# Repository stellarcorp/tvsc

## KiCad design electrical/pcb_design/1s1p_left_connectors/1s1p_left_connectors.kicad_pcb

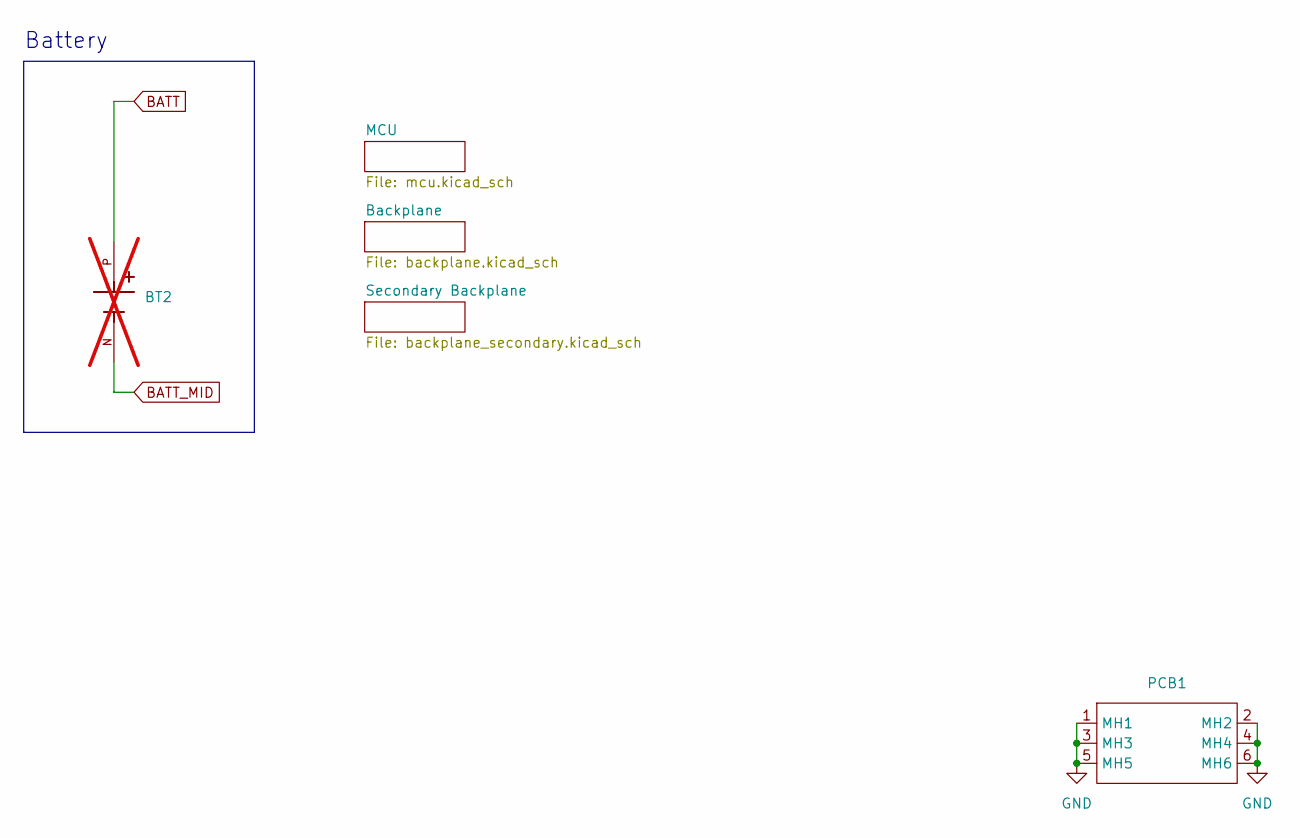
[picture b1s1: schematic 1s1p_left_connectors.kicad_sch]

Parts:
BT2: Keystone_1043; BAT_1043; Manufacturer Part Number 1043; not fitted
PCB1: Interior_Side_Panel_PCB_Shape

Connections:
BATT: BT2.P; also elsewhere on the board
BATT_MID: BT2.N; also elsewhere on the board
GND: PCB1.1 (MH1), PCB1.2 (MH2), PCB1.3 (MH3), PCB1.4 (MH4), PCB1.5 (MH5), PCB1.6 (MH6); also elsewhere on the board

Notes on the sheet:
Battery

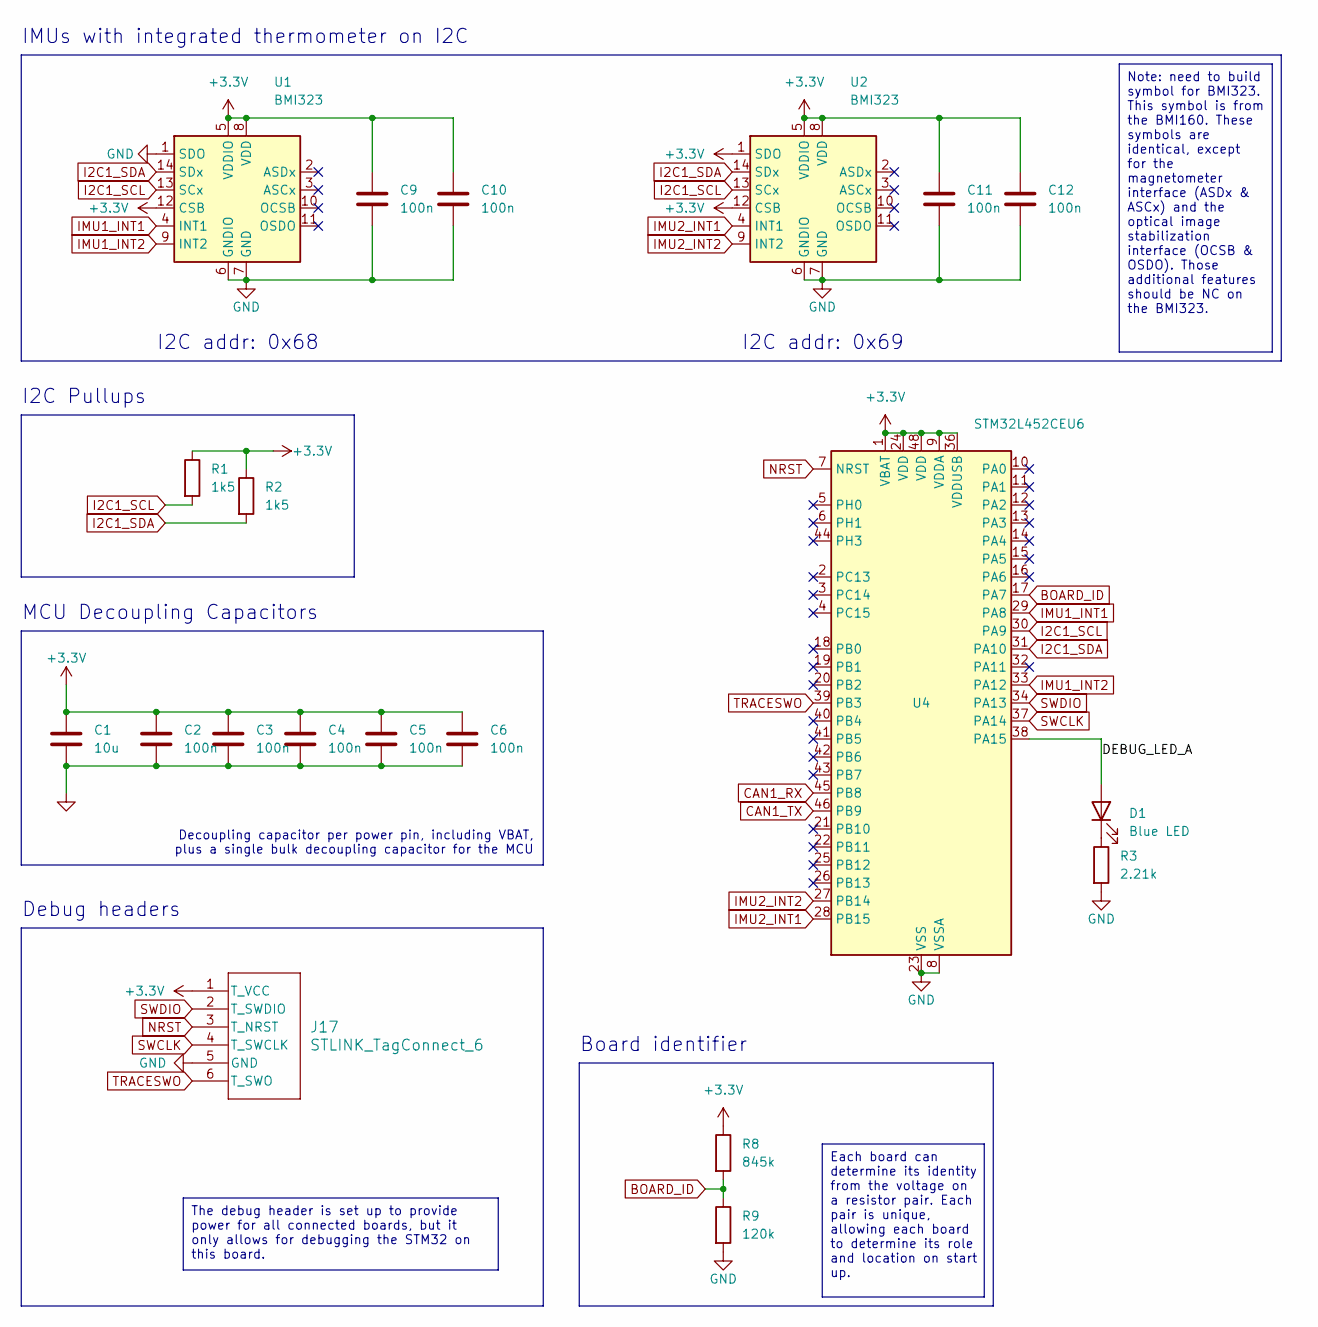
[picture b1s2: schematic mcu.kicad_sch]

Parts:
C1: 10u; C_0603_1608Metric; MPN C344022
C2, C3, C4, C5, C6: 100n; Nondescript_C_0402_1005Metric; MPN C2649549
C9, C10, C11, C12: 100n; Nondescript_C_0402_1005Metric; Manufacturer Part Number GCM155R71H104KE02J
D1: Blue LED; LED_0603_1608Metric; MPN C72041
J17: STLINK_TagConnect_6; Tag-Connect_TC2030-IDC-NL_2x03_P1.27mm_Vertical
R1, R2: 1k5; R_0402_1005Metric; MPN C25867
R3: 2.21k; Nondescript_R_0402_1005Metric; MPN C305298
R8: 845k; Nondescript_R_0402_1005Metric; MPN C270578
R9: 120k; Nondescript_R_0402_1005Metric; MPN C966870
U1, U2: BMI323; Bosch_LGA-14_3x2.5mm_P0.5mm; MPN C5368700
U4: STM32L452CEU6; QFN-48-1EP_7x7mm_P0.5mm_EP5.6x5.6mm_ThermalVias; MPN C222355

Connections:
+3.3V: C1.1, C2.1, C3.1, C4.1, C5.1, C6.1, C9.1, C10.1, C11.1, C12.1, J17.1 (T_VCC), R1.1, R2.1, R8.1, U1.5 (VDDIO), U1.8 (VDD), U1.12 (CSB), U2.1 (SDO), U2.5 (VDDIO), U2.8 (VDD), U2.12 (CSB), U4.1 (VBAT), U4.9 (VDDA), U4.24 (VDD), U4.36 (VDDUSB), U4.48 (VDD); also elsewhere on the board
/MCU/DEBUG_LED_A: D1.2 (A), U4.38 (PA15)
BOARD_ID: R8.2, R9.1, U4.17 (PA7)
CAN1_RX: U4.45 (PB8); also elsewhere on the board
CAN1_TX: U4.46 (PB9); also elsewhere on the board
GND: C1.2, C2.2, C3.2, C4.2, C5.2, C6.2, C9.2, C10.2, C11.2, C12.2, J17.5 (GND), R3.2, R9.2, U1.1 (SDO), U1.6 (GNDIO), U1.7 (GND), U2.6 (GNDIO), U2.7 (GND), U4.8 (VSSA), U4.23 (VSS), U4.35 (VSS), U4.47 (VSS), U4.49 (VSS); also elsewhere on the board
I2C1_SCL: R1.2, U1.13 (SCx), U2.13 (SCx), U4.30 (PA9)
I2C1_SDA: R2.2, U1.14 (SDx), U2.14 (SDx), U4.31 (PA10)
IMU1_INT1: U1.4 (INT1), U4.29 (PA8)
IMU1_INT2: U1.9 (INT2), U4.33 (PA12)
IMU2_INT1: U2.4 (INT1), U4.28 (PB15)
IMU2_INT2: U2.9 (INT2), U4.27 (PB14)
NRST: J17.3 (T_NRST), U4.7 (NRST)
unnamed: D1.1 (K), R3.1
SWCLK: J17.4 (T_SWCLK), U4.37 (PA14)
SWDIO: J17.2 (T_SWDIO), U4.34 (PA13)
TRACESWO: J17.6 (T_SWO), U4.39 (PB3)

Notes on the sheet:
The debug header is set up to provide power for all connected boards, but it only allows for debugging the STM32 on this board.
Note: need to build symbol for BMI323. This symbol is from the BMI160. These symbols are identical, except for the magnetometer interface (ASDx & ASCx) and the optical image stabilization interface (OCSB & OSDO). Those additional features should be NC on the BMI323.
Each board can determine its identity from the voltage on a resistor pair. Each pair is unique, allowing each board to determine its role and location on start up.
I2C addr: 0x68
Debug headers
Board identifier
MCU Decoupling Capacitors
Decoupling capacitor per power pin, including VBAT, plus a single bulk decoupling capacitor for the MCU
IMUs with integrated thermometer on I2C
I2C Pullups
I2C addr: 0x69

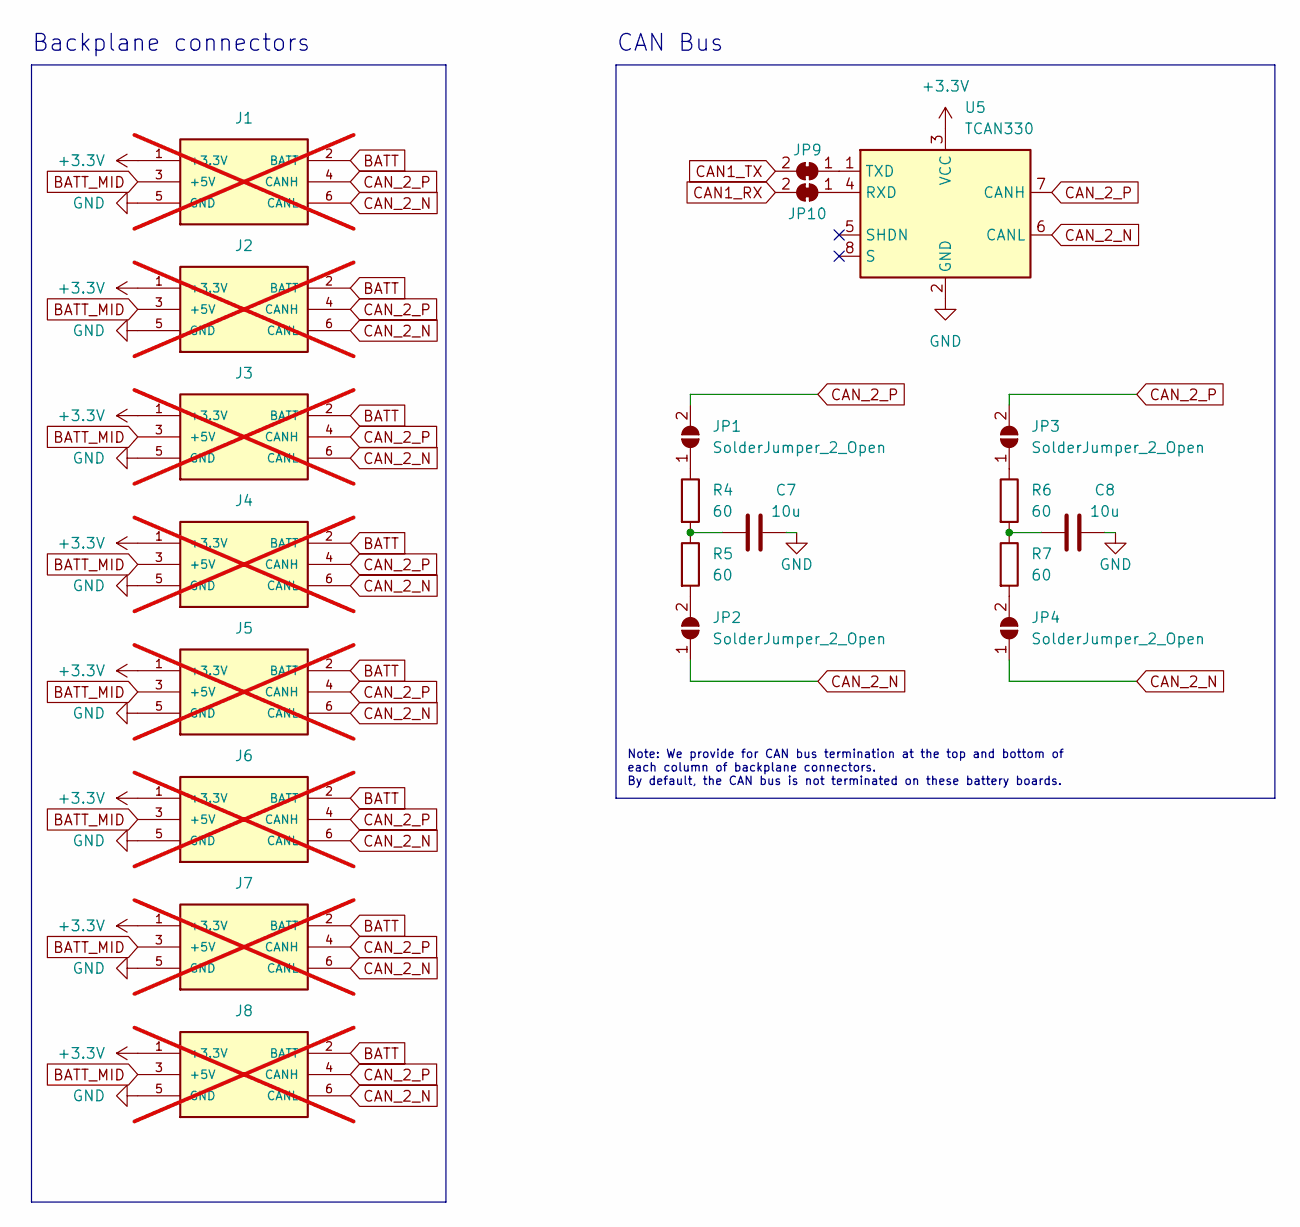
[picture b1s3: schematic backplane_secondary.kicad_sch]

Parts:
C7, C8: 10u; C_0603_1608Metric; MPN C19702
J1, J2, J3, J4, J5, J6, J7, J8: TE_Connectivity_7-5530843-7; Manufacturer Part Number 7-5530843-7; not fitted
JP1, JP2, JP3, JP4: SolderJumper_2_Open; SolderJumper-2_P1.3mm_Open_RoundedPad1.0x1.5mm
JP9, JP10: SolderJumper_2_Bridged; SolderJumper-2_P1.3mm_Bridged_RoundedPad1.0x1.5mm
R4, R5, R6, R7: 60; R_0402_1005Metric
U5: TCAN330; SOT-23-8; Manufacturer Part Number TCAN330DCNR

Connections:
+3.3V: J1.1 (+3.3V), J2.1 (+3.3V), J3.1 (+3.3V), J4.1 (+3.3V), J5.1 (+3.3V), J6.1 (+3.3V), J7.1 (+3.3V), J8.1 (+3.3V), U5.3 (VCC); also elsewhere on the board
BATT: J1.2 (BATT), J2.2 (BATT), J3.2 (BATT), J4.2 (BATT), J5.2 (BATT), J6.2 (BATT), J7.2 (BATT), J8.2 (BATT); also elsewhere on the board
BATT_MID: J1.3 (+5V), J2.3 (+5V), J3.3 (+5V), J4.3 (+5V), J5.3 (+5V), J6.3 (+5V), J7.3 (+5V), J8.3 (+5V); also elsewhere on the board
CAN1_RX: JP10.2 (B); also elsewhere on the board
CAN1_TX: JP9.2 (B); also elsewhere on the board
CAN_2_N: J1.6 (CANL), J2.6 (CANL), J3.6 (CANL), J4.6 (CANL), J5.6 (CANL), J6.6 (CANL), J7.6 (CANL), J8.6 (CANL), JP2.1 (A), JP4.1 (A), U5.6 (CANL)
CAN_2_P: J1.4 (CANH), J2.4 (CANH), J3.4 (CANH), J4.4 (CANH), J5.4 (CANH), J6.4 (CANH), J7.4 (CANH), J8.4 (CANH), JP1.2 (B), JP3.2 (B), U5.7 (CANH)
GND: C7.2, C8.2, J1.5 (GND), J2.5 (GND), J3.5 (GND), J4.5 (GND), J5.5 (GND), J6.5 (GND), J7.5 (GND), J8.5 (GND), U5.2 (GND); also elsewhere on the board
unnamed: C7.1, R4.2, R5.1
unnamed: C8.1, R6.2, R7.1
unnamed: JP1.1 (A), R4.1
unnamed: JP2.2 (B), R5.2
unnamed: JP3.1 (A), R6.1
unnamed: JP4.2 (B), R7.2
unnamed: JP9.1 (A), U5.1 (TXD)
unnamed: JP10.1 (A), U5.4 (RXD)

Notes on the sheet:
Note: We provide for CAN bus termination at the top and bottom of each column of backplane connectors. By default, the CAN bus is not terminated on these battery boards.
CAN Bus
Backplane connectors

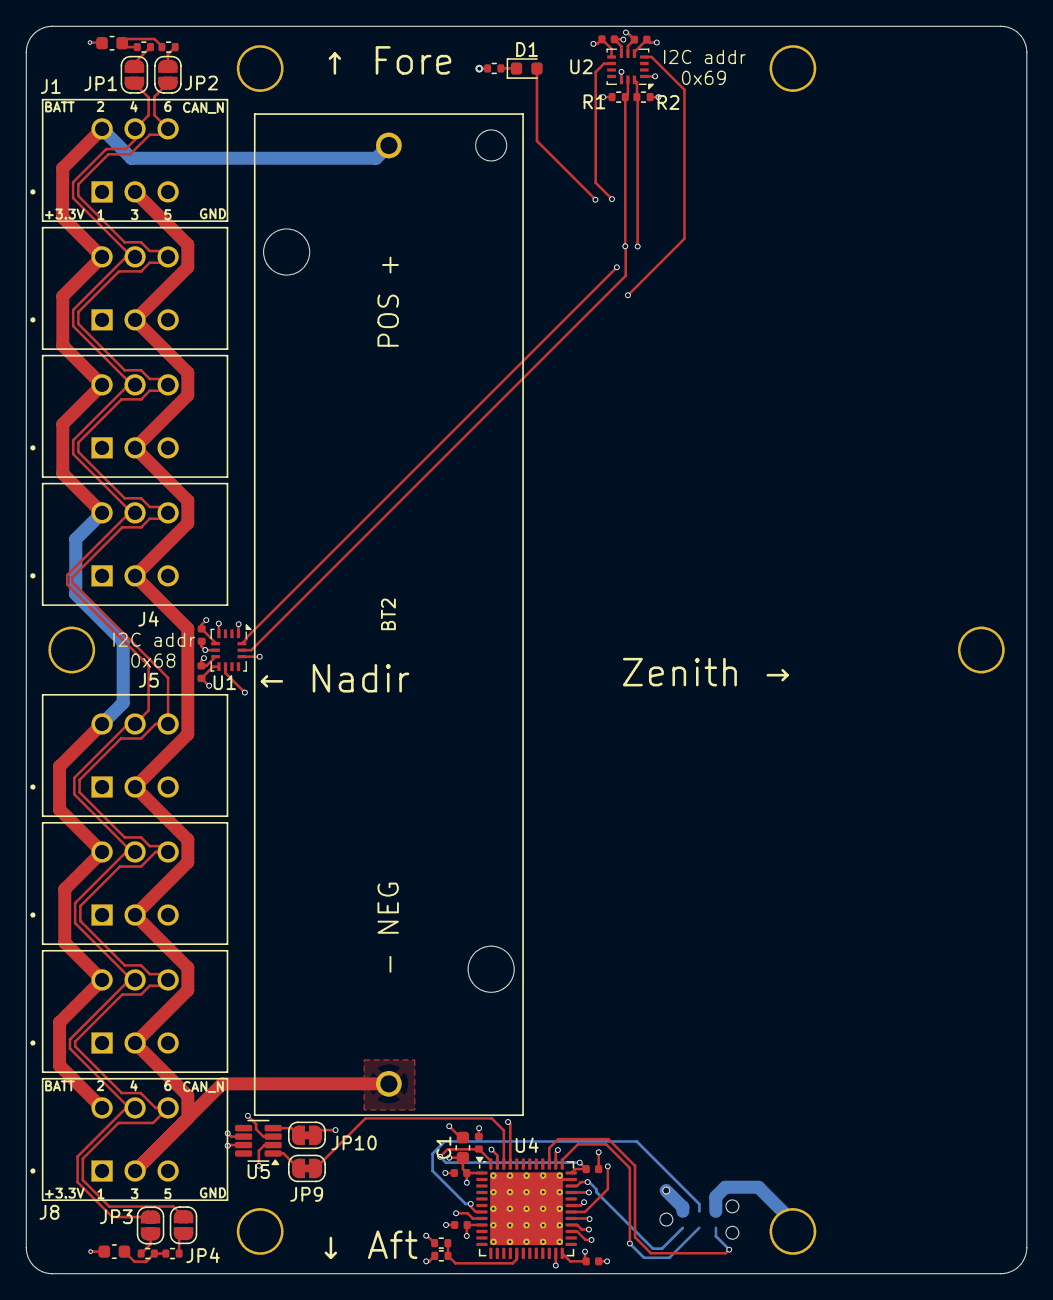
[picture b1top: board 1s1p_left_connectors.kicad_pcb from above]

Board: 4 copper layers, 77.0 x 96.0 mm, 43 parts (1 on the bottom side), 29 nets.

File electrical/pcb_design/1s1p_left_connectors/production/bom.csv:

Designator,Footprint,Quantity,Value,LCSC Part #
C1,0603,1,10u,C344022
"C10, C11, C12, C2, C3, C4, C5, C6, C9",Nondescript_C_0402_1005Metric,9,100n,C2649549
"C7, C8",0603,2,10u,C19702
D1,0603,1,Blue LED,C72041
"JP1, JP2, JP3, JP4",SolderJumper-2_P1.3mm_Open_RoundedPad1.0x1.5mm,4,SolderJumper_2_Open,
"JP10, JP9",SolderJumper-2_P1.3mm_Bridged_RoundedPad1.0x1.5mm,2,SolderJumper_2_Bridged,
"R1, R2",0402,2,1k5,C25867
R3,Nondescript_R_0402_1005Metric,1,2.21k,C305298
"R4, R5, R6, R7",0402,4,60,
R8,Nondescript_R_0402_1005Metric,1,845k,C270578
R9,Nondescript_R_0402_1005Metric,1,120k,C966870
"U1, U2",Bosch_LGA-14_3x2.5mm_P0.5mm,2,BMI323,C5368700
U4,QFN-48-1EP_7x7mm_P0.5mm_EP5.6x5.6mm_ThermalVias,1,STM32L452CEU6,C222355
U5,SOT-23-8,1,TCAN330,C2877587

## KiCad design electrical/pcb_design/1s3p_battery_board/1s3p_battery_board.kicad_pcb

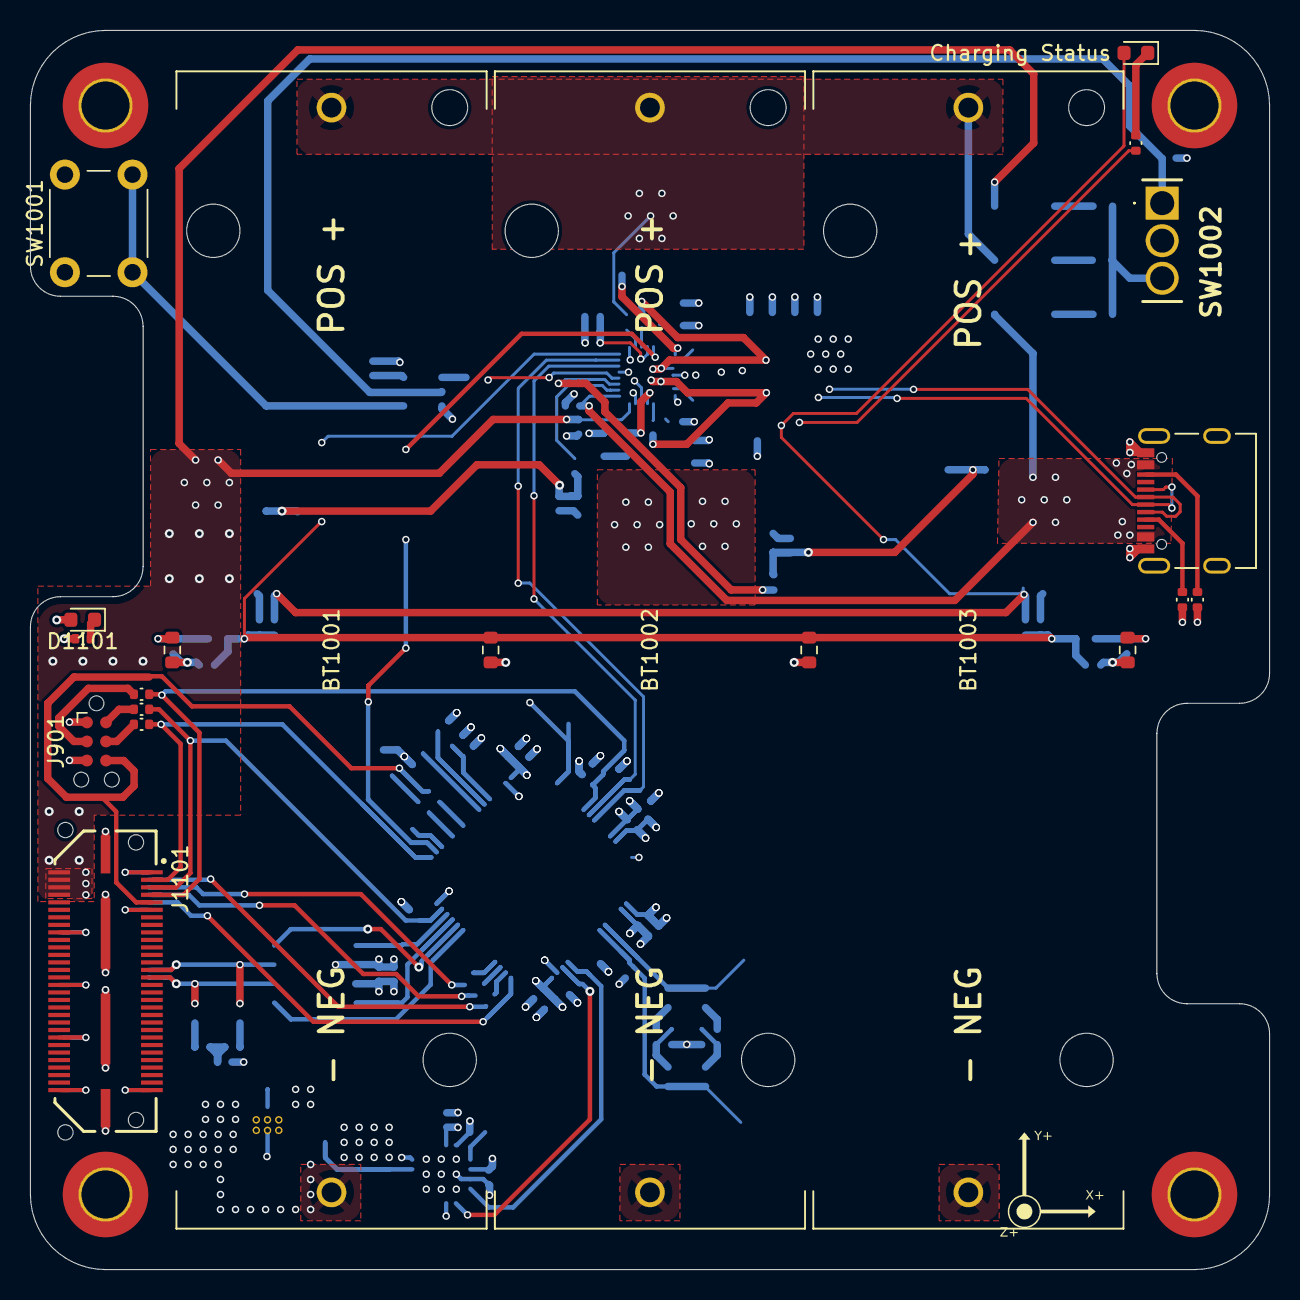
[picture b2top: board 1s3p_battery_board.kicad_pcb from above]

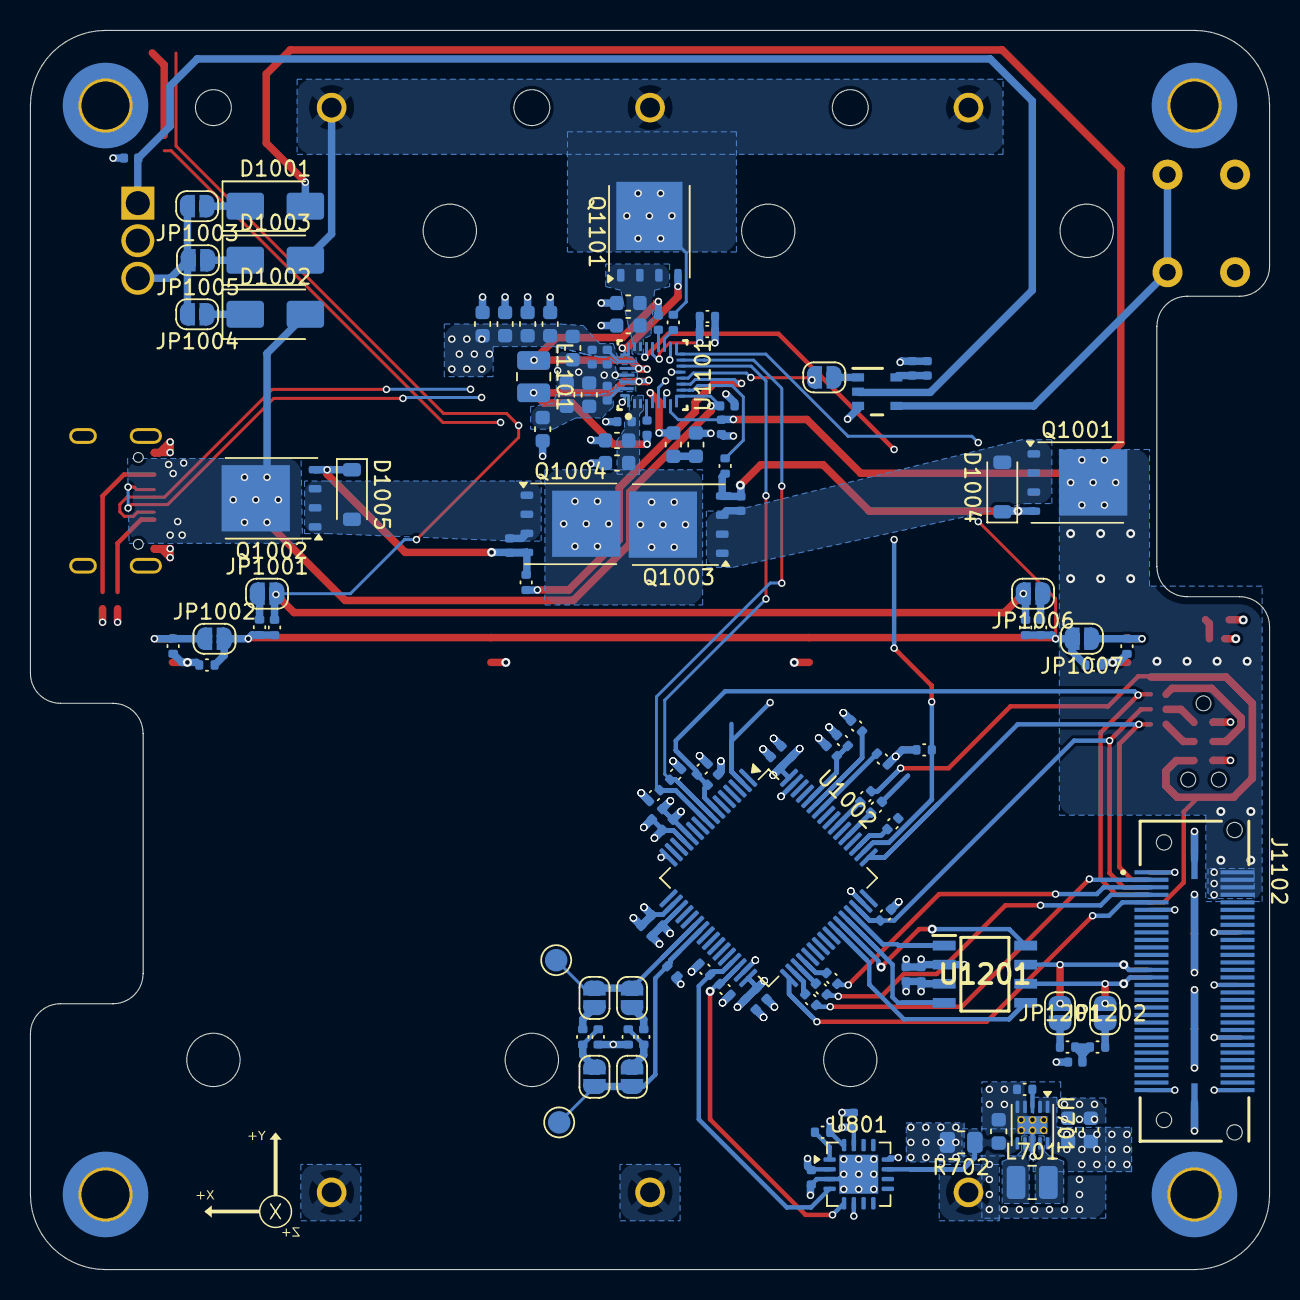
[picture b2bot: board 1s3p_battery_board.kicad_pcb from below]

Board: 4 copper layers, 82.5 x 82.5 mm, 141 parts (119 on the bottom side), 91 nets.

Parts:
BT1001, BT1002, BT1003: Battery_Cell; BAT_1043
C701, C703: 22u; Nondescript_C_0603_1608Metric
C702, C1101, C1102, C1104, C1105, C1107, C1108, C1111, C1112, C1114, C1116, C1117, C1118, C1119, C1120: 10u; Nondescript_C_0603_1608Metric
C801, C802, C1002, C1003, C1004, C1006, C1010, C1011, C1013, C1014, C1016, C1103, C1106, C1113, C1115, C1202, C1203: 100n; Nondescript_C_0402_1005Metric
C901, C1007, C1008: 1n; Nondescript_C_0402_1005Metric
C1001, C1005, C1009, C1012, C1015, C1017, C1201: 1u; Nondescript_C_0402_1005Metric
C1109, C1110: 0.047u; Nondescript_C_0402_1005Metric
D1001, D1002, D1003: D_SMA
D1004, D1005: Zener; D_SOD-123
D1006: Charging Status; LED_0603_1608Metric
D1101: Debug; LED_0603_1608Metric
J901: STLINK; Tag-Connect_TC2030-IDC-NL_2x03_P1.27mm_Vertical
J1101: QTH-030-07-L-D-A; SAMTEC_QTH-030-07-L-D-A
J1102: QSH-030-01-L-D-A; SAMTEC_QSH-030-01-L-D-A
J1201: USB_C_Receptacle; AMPHENOL_10155435-00011LF
JP901, JP902, JP1001, JP1002, JP1003, JP1004, JP1005, JP1006, JP1007, JP1008, JP1201, JP1202: SolderJumper_2_Open; SolderJumper-2_P1.3mm_Open_RoundedPad1.0x1.5mm
JP903: 0x10; SolderJumper-2_P1.3mm_Open_RoundedPad1.0x1.5mm
JP904: 0xEF; SolderJumper-2_P1.3mm_Open_RoundedPad1.0x1.5mm
L701, L1101: 2.2µH; L_1008_2520Metric
PCB1101: Core_Board
Q1001, Q1002, Q1003, Q1004, Q1101: CSD16570Q5B; TDSON-8-1
R101, R801, R1002, R1006, R1007, R1008, R1020, R1022, R1023, R1024, R1026, R1101, R1102: 9k31; Nondescript_R_0402_1005Metric
R701: 36k5; Nondescript_R_0402_1005Metric
R702: 100m; R_0805_2012Metric
R901, R902, R903, R1004, R1005, R1017, R1018, R1019, R1021, R1025, R1103: 33; Nondescript_R_0402_1005Metric
R904, R907: 23k2; Nondescript_R_0402_1005Metric
R905, R906: 1k58; Nondescript_R_0402_1005Metric
R1001, R1009, R1011, R1014: 57k9; Nondescript_R_0402_1005Metric
R1003, R1010, R1012, R1015: 7k2; Nondescript_R_0402_1005Metric
R1013, R1016: 294; Nondescript_R_0402_1005Metric
R1104: 100; Nondescript_R_0402_1005Metric
R1201, R1202: 5k1; Nondescript_R_0402_1005Metric
R1203, R1204: 60; Nondescript_R_0402_1005Metric
SW1001: System Reset; SW_PUSH_6mm
SW1002: RBF Tag Mimic; D2MQ1L105
TH1001, TH1002, TH1003, TH1004: 10k NTC; Nondescript_R_0603_1608Metric
TP901: BOARD_ID_SENSE; TestPoint_Pad_D1.5mm
TP902: BOARD_ID_POWER; TestPoint_Pad_D1.5mm
U701: TPS63900; WSON-10-1EP_2.5x2.5mm_P0.5mm_EP1.2x2mm_ThermalVias
U801: PAC1934T-I/JQ; UQFN-16-1EP_4x4mm_P0.65mm_EP2.6x2.6mm
U1001: TPS3840DL36DBVR; DBV0005A_L
U1002: STM32L452RCTx; LQFP-64_10x10mm_P0.5mm
U1101: BQ25798; RQM0029A-MFG
U1201: TCAN330DR; SOIC127P600X175-8N

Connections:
/3V3: C801.1, C802.1, C1009.1, C1011.1, C1012.1, C1013.1, C1014.1, C1015.1, C1016.1, C1017.1, C1201.1, C1202.1, J901.1 (T_VCC), R101.1, R702.2, R801.1, R1002.1, R1006.1, R1008.1, R1020.1, R1022.1, R1023.1, R1024.1, R1026.1, U801.2 (V_{DD}), U801.12 (SENSE1-), U801.15 (V_{DD}IO), U801.16 (~PWRDN), U1002.13 (VDDA), U1002.19 (VDD), U1002.32 (VDD), U1002.64 (VDD), U1201.3 (VCC)
/Batteries/1S Battery Charger/BATT_TEMP: JP1002.2 (B), JP1007.2 (B), R1003.2, R1009.1, R1010.2, R1011.1, R1012.2, R1015.2, TH1002.1, TH1003.1, U1101.16 (TS)
/Batteries/1S Battery Charger/BATT_VIN: C1101.1, C1102.1, C1103.1, Q1003.5 (D), Q1004.5 (D), U1101.2 (VBUS), U1101.3 (VBUS)
/Batteries/1S Battery Charger/EXTERNAL_DRV: R1013.2, U1101.10 (ACDRV2)
/Batteries/1S Battery Charger/STAT: R1021.2, U1101.1 (STAT)
/Batteries/1S Battery Charger/SYS_INHIBIT_N: JP1008.2 (B), U1101.12 (~QON)
/Batteries/1S Battery Charger/USB_D+: J1201.A6 (D+_1), J1201.B6 (D+_2), U1101.6 (D+)
/Batteries/1S Battery Charger/USB_D-: J1201.A7 (D-_1), J1201.B7 (D-_2), U1101.7 (D-)
/Batteries/1S Battery Charger/USB_DRV: R1016.2, U1101.11 (ACDRV1)
/Batteries/BATT_INT: R101.2, U1002.50 (PA15), U1101.21 (~INT)
/Batteries/EXTERNAL_VIN: C1003.1, D1001.2 (A), J1101.02, J1101.04, J1101.06, J1101.08, J1102.02, J1102.04, J1102.06, J1102.08, Q1001.5 (D), U1101.8 (VAC2)
/Batteries/EXTERNAL_VIN_MON: D1001.1 (K), JP1003.1 (A)
/Batteries/I2C_SCL: R1002.2, U1002.8 (PC0), U1101.14 (SCL)
/Batteries/I2C_SDA: R1008.2, U1002.9 (PC1), U1101.15 (SDA)
/Batteries/REGN: C1104.1, D1006.2 (A), JP1001.2 (B), JP1006.2 (B), R1010.1, R1012.1, U1101.5 (REGN), U1101.17 (ILIM_HIZ)
/Batteries/USB_VIN: C1006.1, D1002.2 (A), J1201.A4 (VBUS_1), J1201.B4 (VBUS_3), Q1002.5 (D), U1101.9 (VAC1)
/Batteries/USB_VIN_MON: D1002.1 (K), JP1004.1 (A)
/Batteries/VBATT: BT1001.P, BT1002.P, BT1003.P, D1003.2 (A), Q1101.5 (D), R1104.2
/Batteries/VBATT_MON: D1003.1 (K), JP1005.1 (A)
/Batteries/VBUS: C701.1, C702.1, C1113.1, C1115.1, C1116.1, C1117.1, C1118.1, C1119.1, C1120.1, J1101.01, J1101.18, J1101.32, J1101.46, J1101.60, J1102.01, J1102.18, J1102.32, J1102.46, J1102.60, U701.1 (EN), U701.2 (SEL), U701.10 (VIN), U1101.25 (SYS)
/Board Identification/BOARD_ID_POWER: JP903.1 (A), JP904.1 (A), TP902.1, U1002.22 (PA6)
/Board Identification/BOARD_ID_SENSE: C901.2, JP901.1 (A), JP902.1 (A), TP901.1, U1002.23 (PA7)
/Core Board/CAN bus/CANH_TERMINATION: JP1201.2 (B), R1203.1
/Core Board/CAN bus/CANL_TERMINATION: JP1202.1 (A), R1204.2
/Core Board/CAN bus/CAN_RX: U1002.44 (PA11), U1201.4 (RXD)
/Core Board/CAN bus/CAN_SHUTDOWN: U1002.42 (PA9), U1201.5 (SHDN)
/Core Board/CAN bus/CAN_SILENT: U1002.43 (PA10), U1201.8 (S)
/Core Board/CAN bus/CAN_TX: U1002.45 (PA12), U1201.1 (TXD)
/Core Board/CANH: J1101.27, J1102.27, JP1201.1 (A), U1201.7 (CANH)
/Core Board/CANL: J1101.29, J1102.29, JP1202.2 (B), U1201.6 (CANL)
/Core Board/CTRL.NRST: J1102.07, R1018.2
/Core Board/CTRL.SWCLK: J1102.03, R1017.2
/Core Board/CTRL.SWDIO: J1102.05, R1019.2
/Core Board/CTRL.SWO: J1102.09, U1002.33 (PB12)
/Core Board/I2C1_SCL: R1022.2, U1002.58 (PB6)
/Core Board/I2C1_SDA: R1026.2, U1002.59 (PB7)
/Core Board/I2C2_SCL: R1020.2, U801.4 (SCL), U1002.29 (PB10)
/Core Board/I2C2_SDA: R1023.2, U801.5 (SDA), U1002.30 (PB11)
/Core Board/MCU/BOOT0: C1002.1, R1007.1, U1002.60 (PH3)
/Core Board/MCU/DEBUG_LED: D1101.2 (A), U1002.2 (PC13)
/Core Board/NRST: C1004.1, J1101.07, R902.1, R1006.2, U1002.7 (NRST)
/Core Board/Power Measurement/BOARD_LOAD_+: C703.1, R702.1, U701.6 (VOUT), U801.11 (SENSE1+)
/Core Board/SWCLK: J1101.03, R903.1, U1002.49 (PA14)
/Core Board/SWDIO: J1101.05, R901.1, R1024.2, U1002.46 (PA13)
/Core Board/SWO: J901.6 (T_SWO), J1101.09, R1025.2
GND: BT1001.N, BT1002.N, BT1003.N, C701.2, C702.2, C703.2, C801.2, C802.2, C901.1, C1001.2, C1002.2, C1003.2, C1004.2, C1005.2, C1006.2, C1009.2, C1010.2, C1011.2, C1012.2, C1013.2, C1014.2, C1015.2, C1016.2, C1017.2, C1101.2, C1102.2, C1103.2, C1105.2, C1106.2, C1107.2, C1108.2, C1111.2, C1112.2, C1113.2, C1114.2, C1115.2, C1116.2, C1117.2, C1118.2, C1119.2, C1120.2, C1201.2, C1202.2, C1203.1, J901.5 (GND), J1101.11, J1101.59, J1101.G1 (GND), J1101.G2 (GND__1), J1101.G3 (GND__2), J1101.G4 (GND__3), J1102.11, J1102.59, J1102.S1 (GND), J1102.S2 (GND__1), J1102.S3 (GND__2), J1102.S4 (GND__3), J1201.A1 (GND_1), J1201.B1 (GND_3), J1201.MH1, J1201.MH2, J1201.MH3, J1201.MH4, PCB1101.MH1, PCB1101.MH2, PCB1101.MH3, PCB1101.MH4, R701.2, R905.2, R907.2, R1001.2, R1007.2, R1009.2, R1011.2, R1014.2, R1101.2, R1102.2, R1103.2, R1201.2, R1202.2, SW1001.1, SW1002.2 (NO), TH1001.2, TH1002.2, TH1003.2, TH1004.2, U701.4 (CFG2), U701.5 (CFG3), U701.8 (GND), U701.11 (GND), U801.3 (GND), U801.6 (ADDRSEL), U801.17 (EP), U1001.3 (GND), U1002.12 (VSSA), U1002.16 (PA2), U1002.18 (VSS), U1002.31 (VSS), U1002.47 (VSS), U1002.63 (VSS), U1101.13 (~CE), U1101.27 (GND), U1201.2 (GND)
unnamed: C1104.2, C1105.1
unnamed: C1111.1, C1114.1, Q1101.1 (S), Q1101.2 (S), Q1101.3 (S), U1101.22 (BAT), U1101.23 (BAT)
unnamed: C1203.2, R1203.2, R1204.1
unnamed: C1007.1, D1004.2 (A), Q1001.1 (S), Q1001.2 (S), Q1001.3 (S), Q1003.1 (S), Q1003.2 (S), Q1003.3 (S)
unnamed: C1007.2, D1004.1 (K), Q1001.4 (G), Q1003.4 (G), R1013.1
unnamed: C1008.1, D1005.2 (A), Q1002.1 (S), Q1002.2 (S), Q1002.3 (S), Q1004.1 (S), Q1004.2 (S), Q1004.3 (S)
unnamed: C1008.2, D1005.1 (K), Q1002.4 (G), Q1004.4 (G), R1016.1
unnamed: D1006.1 (K), R1021.1
unnamed: D1101.1 (K), R1103.1
unnamed: J901.3 (T_NRST), R902.2
unnamed: J901.4 (T_SWCLK), R903.2
unnamed: J901.2 (T_SWDIO), R901.2
unnamed: J1201.A5 (CC1), R1201.1
unnamed: J1201.B5 (CC2), R1202.1
unnamed: JP901.2 (B), R904.2, R905.1
unnamed: JP902.2 (B), R906.2, R907.1
unnamed: JP903.2 (B), R904.1
unnamed: JP904.2 (B), R906.1
unnamed: JP1001.1 (A), R1003.1
unnamed: JP1002.1 (A), R1001.1, TH1001.1
unnamed: JP1003.2 (B), JP1004.2 (B), JP1005.2 (B), SW1002.3 (NC)
unnamed: JP1006.1 (A), R1015.1
unnamed: JP1007.1 (A), R1014.1, TH1004.1
unnamed: JP1008.1 (A), U1001.1 (RESET_N)
unnamed: Q1101.4 (G), U1101.24 (SDRV)
unnamed: C1010.1, SW1002.1 (COM), U1001.2 (VDD)
unnamed: R701.1, U701.3 (CFG1)
unnamed: L701.2, U701.9 (LX1)
unnamed: L701.1, U701.7 (LX2)
unnamed: R801.2, U801.1 (SLOW)
unnamed: C1001.1, C1005.1, U1001.5 (CT)
unnamed: SW1001.2, U1001.4 (MR_N)
unnamed: R1025.1, U1002.55 (PB3)
unnamed: R1017.1, U1002.34 (PB13)
unnamed: R1018.1, U1002.35 (PB14)
unnamed: R1019.1, U1002.36 (PB15)
unnamed: R1004.2, U1002.51 (PC10)
unnamed: R1005.2, U1002.53 (PC12)
unnamed: R1104.1, U1101.18 (BATP)
unnamed: C1109.1, U1101.4 (BTST1)
unnamed: C1110.1, U1101.19 (BTST2)
unnamed: C1106.1, C1107.1, C1108.1, C1112.1, U1101.29 (PMID)
unnamed: R1101.1, R1102.1, U1101.20 (PROG)
unnamed: C1109.2, L1101.2, U1101.28 (SW1)
unnamed: C1110.2, L1101.1, U1101.26 (SW2)

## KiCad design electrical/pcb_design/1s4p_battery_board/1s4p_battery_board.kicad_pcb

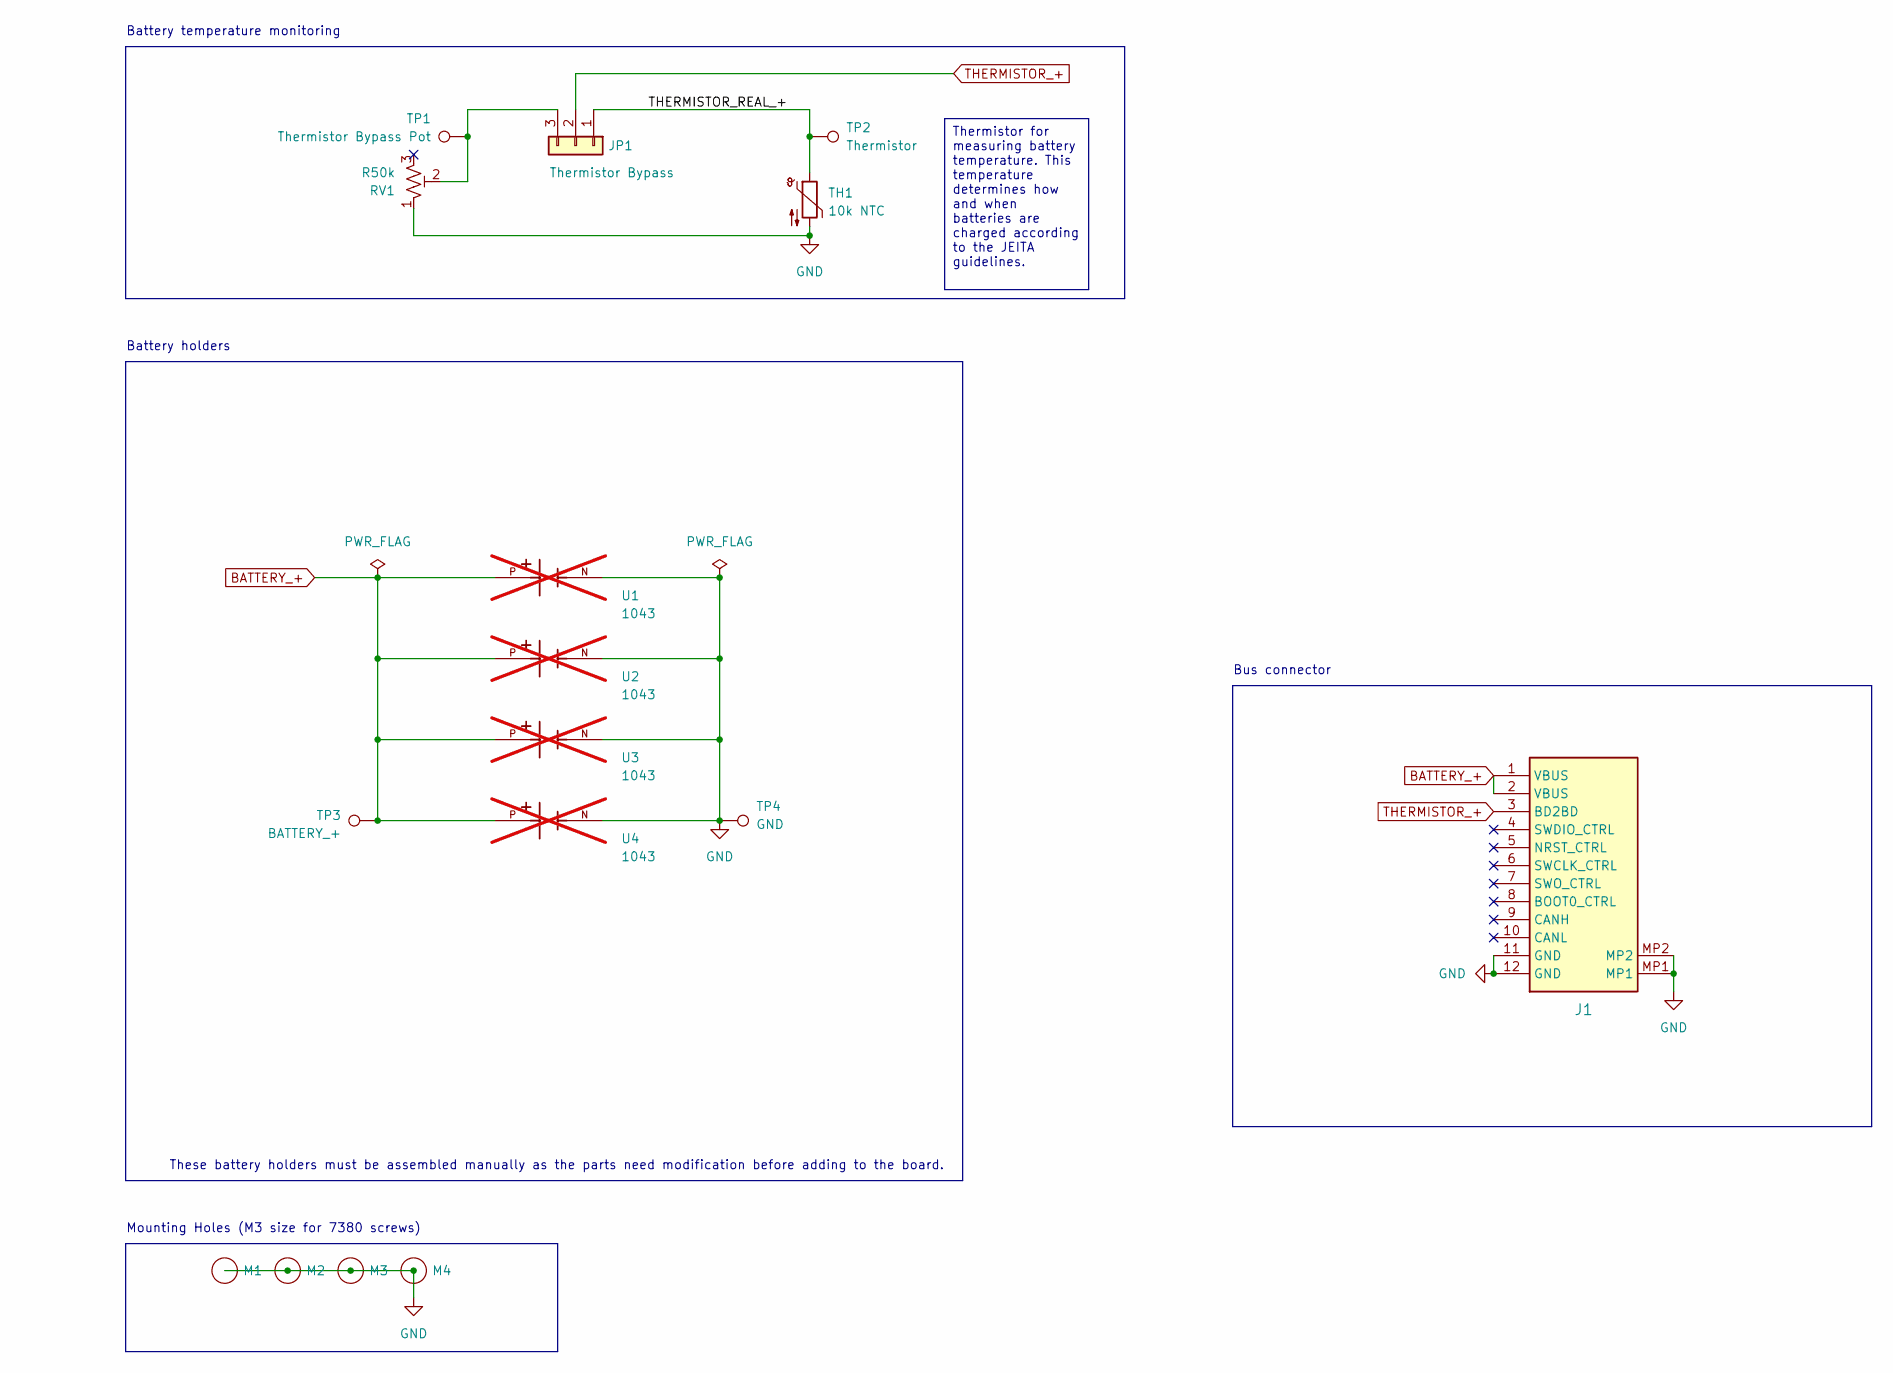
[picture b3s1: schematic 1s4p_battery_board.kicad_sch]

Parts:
J1: Molex_504050-1291; Bus Connector (Control); MPN C563982
JP1: Conn_01x03; HDRV3W64P0X254_1X3_762X254X869P; MPN C2915006
M1, M2, M3, M4: MountingHole_3.2mm_M3_ISO7380_Pad_TopBottom; MPN NA
RV1: R50k; Potentiometer_Bourns_3314J_Vertical; MPN C50895
TH1: 10k NTC; Nondescript_R_0402_1005Metric; MPN C336815
TP1: Thermistor Bypass Pot; TestPoint_Pad_D1.5mm; MPN NA
TP2: Thermistor; TestPoint_Pad_D1.5mm; MPN NA
TP3: BATTERY_+; TestPoint_Pad_D1.5mm; MPN NA
TP4: GND; TestPoint_Pad_D1.5mm; MPN NA
U1, U2, U3, U4: 1043; BAT_1043; Manufacturer Part Number 1043; not fitted

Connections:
/THERMISTOR_REAL_+: JP1.1, TH1.1, TP2.1
BATTERY_+: J1.1 (VBUS), J1.2 (VBUS), TP3.1, U1.P, U2.P, U3.P, U4.P
GND: J1.11 (GND), J1.12 (GND), J1.MP1, J1.MP2, M1.1 (Hole), M2.1 (Hole), M3.1 (Hole), M4.1 (Hole), RV1.1, TH1.2, TP4.1, U1.N, U2.N, U3.N, U4.N
unnamed: JP1.3, RV1.2, TP1.1
THERMISTOR_+: J1.3 (BD2BD), JP1.2

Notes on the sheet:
Thermistor for measuring battery temperature. This temperature determines how and when batteries are charged according to the JEITA guidelines.
Mounting Holes (M3 size for 7380 screws)
Battery temperature monitoring
Battery holders
These battery holders must be assembled manually as the parts need modification before adding to the board.
Bus connector
